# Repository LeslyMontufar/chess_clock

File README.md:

# chess_clock
Relógio de xadrez: esquemático elétrico, código do STM32CubeIDE e PCB.

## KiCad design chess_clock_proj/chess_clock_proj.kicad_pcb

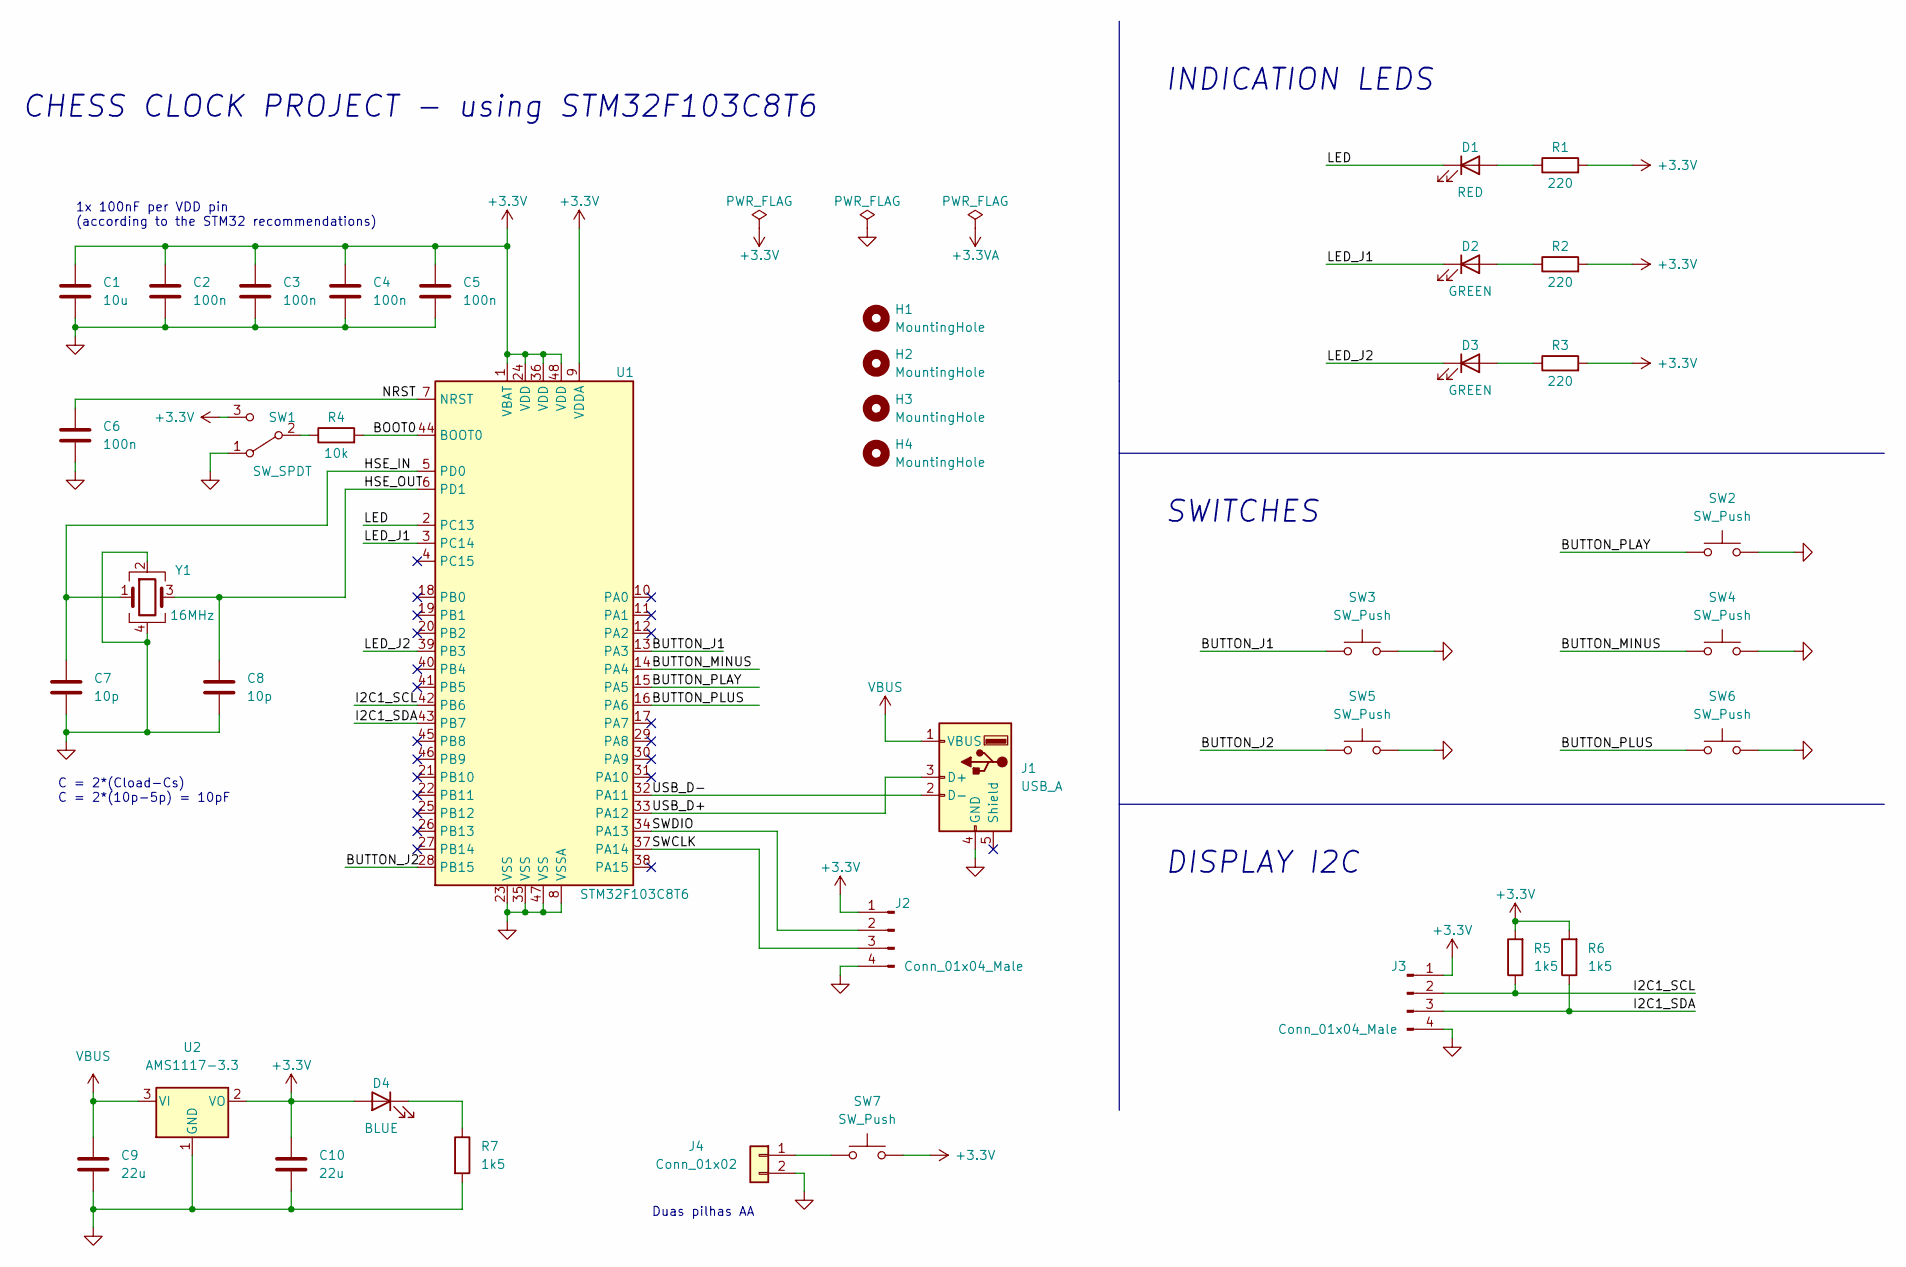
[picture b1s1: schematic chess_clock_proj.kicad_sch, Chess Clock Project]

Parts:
C1: 10u; C_0603_1608Metric
C2, C3, C4, C5, C6: 100n; C_0402_1005Metric
C7, C8: 10p; C_0402_1005Metric
C9, C10: 22u; C_0805_2012Metric
D1: RED; LED_D5.0mm
D2, D3: GREEN; LED_D5.0mm
D4: BLUE; LED_D5.0mm
H1, H2, H3, H4: MountingHole; MountingHole_2.1mm
J1: USB_A; USB_A_Wuerth_614004134726_Horizontal
J2, J3: Conn_01x04_Male; PinHeader_1x04_P2.54mm_Vertical
J4: Conn_01x02; BatteryHolder_MPD_BC12AAPC_2xAA
R1, R2, R3: 220; R_0402_1005Metric
R4: 10k; R_0402_1005Metric
R5, R6, R7: 1k5; R_0402_1005Metric
SW1: SW_SPDT; SW_E-Switch_EG1224_SPDT_Angled
SW2, SW3, SW4, SW5, SW6: SW_Push; SW_PUSH_6mm
SW7: SW_Push; SW_DIP_SPSTx01_Slide_9.78x4.72mm_W7.62mm_P2.54mm
U1: STM32F103C8T6; LQFP-48_7x7mm_P0.5mm
U2: AMS1117-3.3; SOT-223-3_TabPin2
Y1: 16MHz; Crystal_SMD_3225-4Pin_3.2x2.5mm

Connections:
+3V3: C1.1, C2.1, C3.1, C4.1, C5.1, C10.1, D4.2 (A), J2.1, J3.1, R1.2, R2.2, R3.2, R5.2, R6.2, SW1.3 (C), SW7.2, U1.1 (VBAT), U1.9 (VDDA), U1.24 (VDD), U1.36 (VDD), U1.48 (VDD), U2.2 (VO)
/BOOT0: R4.2, U1.44 (BOOT0)
/BUTTON_J1: SW3.1, U1.13 (PA3)
/BUTTON_J2: SW5.1, U1.28 (PB15)
/BUTTON_MINUS: SW4.1, U1.14 (PA4)
/BUTTON_PLAY: SW2.1, U1.15 (PA5)
/BUTTON_PLUS: SW6.1, U1.16 (PA6)
/HSE_IN: C7.1, U1.5 (PD0), Y1.1
/HSE_OUT: C8.1, U1.6 (PD1), Y1.3
/I2C1_SCL: J3.2, R5.1, U1.42 (PB6)
/I2C1_SDA: J3.3, R6.1, U1.43 (PB7)
/LED: D1.1 (K), U1.2 (PC13)
/LED_J1: D2.1 (K), U1.3 (PC14)
/LED_J2: D3.1 (K), U1.39 (PB3)
/NRST: C6.1, U1.7 (NRST)
/SWCLK: J2.3, U1.37 (PA14)
/SWDIO: J2.2, U1.34 (PA13)
/USB_D+: J1.3 (D+), U1.33 (PA12)
/USB_D-: J1.2 (D-), U1.32 (PA11)
GND: C1.2, C2.2, C3.2, C4.2, C5.2, C6.2, C7.2, C8.2, C9.2, C10.2, J1.4 (GND), J2.4, J3.4, J4.2, R7.2, SW1.1 (A), SW2.2, SW3.2, SW4.2, SW5.2, SW6.2, U1.8 (VSSA), U1.23 (VSS), U1.35 (VSS), U1.47 (VSS), U2.1 (GND), Y1.2, Y1.4
unnamed: D1.2 (A), R1.1
unnamed: D2.2 (A), R2.1
unnamed: D3.2 (A), R3.1
unnamed: D4.1 (K), R7.1
unnamed: J4.1, SW7.1
unnamed: R4.1, SW1.2 (B)
VBUS: C9.1, J1.1 (VBUS), U2.3 (VI)

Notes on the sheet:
Duas pilhas AA
1x 100nF per VDD pin (according to the STM32 recommendations)
DISPLAY I2C
INDICATION LEDS
CHESS CLOCK PROJECT - using STM32F103C8T6
C = 2*(Cload-Cs) C = 2*(10p-5p) = 10pF
SWITCHES

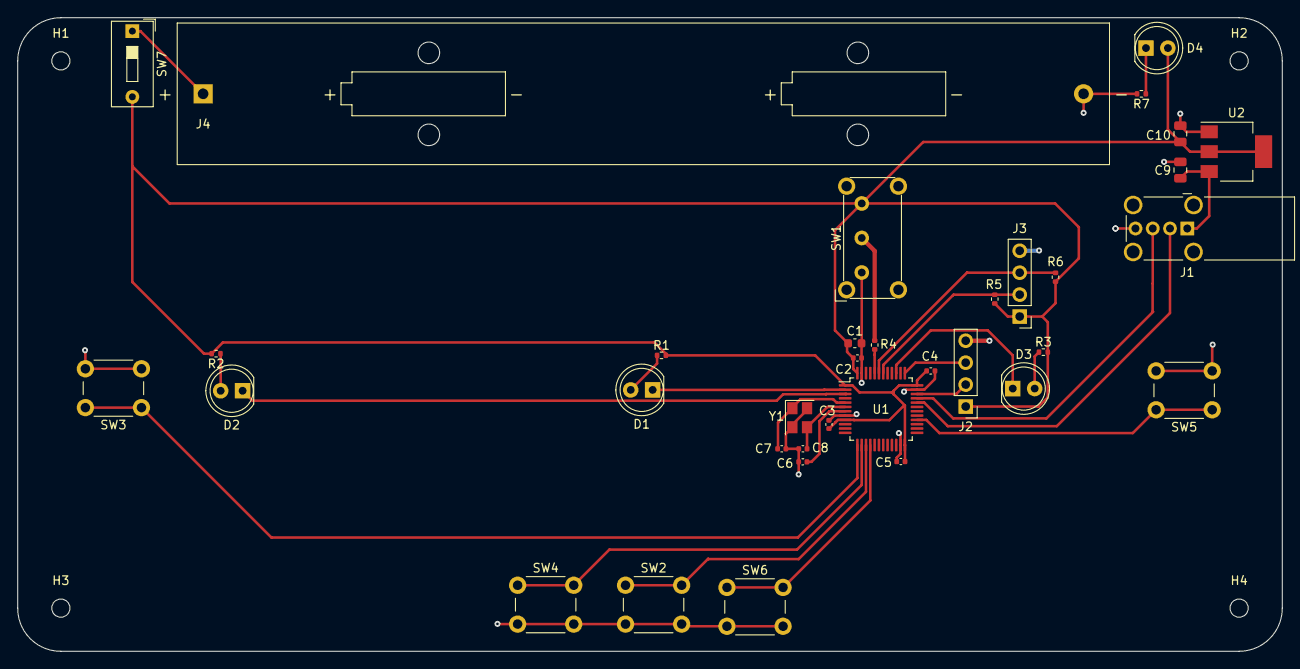
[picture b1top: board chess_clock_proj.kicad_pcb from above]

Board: 2 copper layers, 146.5 x 73.4 mm, 39 parts (0 on the bottom side), 27 nets.

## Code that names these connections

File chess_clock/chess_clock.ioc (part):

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Mcu.Name=STM32F103C(8-B)Tx
Mcu.Package=LQFP48
Mcu.UserName=STM32F103C8Tx
PA0-WKUP.GPIOParameters=GPIO_PuPd,GPIO_Label
PA0-WKUP.GPIO_Label=BUTTON_J1
PA0-WKUP.GPIO_PuPd=GPIO_PULLUP
PA0-WKUP.Signal=GPXTI0
PA1.GPIOParameters=GPIO_PuPd,GPIO_Label
PA1.GPIO_Label=BUTTON_J2
PA1.GPIO_PuPd=GPIO_PULLUP
PA1.Signal=GPXTI1
PA11.Mode=Device
PA11.Signal=USB_DM
PA12.Mode=Device
PA12.Signal=USB_DP
PA13.Mode=Serial_Wire
PA13.Signal=SYS_JTMS-SWDIO
PA14.Mode=Serial_Wire
PA14.Signal=SYS_JTCK-SWCLK
PA4.GPIOParameters=GPIO_PuPd,GPIO_Label
PA4.GPIO_Label=BUTTON_MINUS
PA4.GPIO_PuPd=GPIO_PULLUP
PA4.Signal=GPXTI4
PA5.GPIOParameters=GPIO_PuPd,GPIO_Label
PA5.GPIO_Label=BUTTON_PLUS
PA5.GPIO_PuPd=GPIO_PULLUP
PA5.Signal=GPXTI5
PA6.GPIOParameters=GPIO_PuPd,GPIO_Label
PA6.GPIO_Label=BUTTON_PLAY
PA6.GPIO_PuPd=GPIO_PULLUP
PA6.Signal=GPXTI6
PB10.GPIOParameters=GPIO_Label
PB10.GPIO_Label=LED_J1
PB10.Signal=GPIO_Output
PB11.GPIOParameters=GPIO_Label
PB11.GPIO_Label=LED_J2
PB11.Signal=GPIO_Output
PB6.Mode=I2C
PB6.Signal=I2C1_SCL
PB7.Mode=I2C
PB7.Signal=I2C1_SDA
PC13-TAMPER-RTC.GPIOParameters=GPIO_Label
PC13-TAMPER-RTC.GPIO_Label=LED
PC13-TAMPER-RTC.Signal=GPIO_Output
PD0-OSC_IN.Mode=HSE-External-Oscillator
PD0-OSC_IN.Signal=RCC_OSC_IN
PD1-OSC_OUT.Mode=HSE-External-Oscillator
PD1-OSC_OUT.Signal=RCC_OSC_OUT
RCC.HSEDivPLL=RCC_HSE_PREDIV_DIV2
RCC.HSE_VALUE=16000000
RCC.SYSCLKFreq_VALUE=72000000
RCC.SYSCLKSource=RCC_SYSCLKSOURCE_PLLCLK
board=custom

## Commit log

2022-07-27 Início do projeto: código (stm32cubeIDE) e esquemático (KiCad)
2022-08-01 conexões feitas
2022-08-19 Terminei
2022-08-21 alterei a posição da malha de terra, e retirei o resistor próximo ao USB
